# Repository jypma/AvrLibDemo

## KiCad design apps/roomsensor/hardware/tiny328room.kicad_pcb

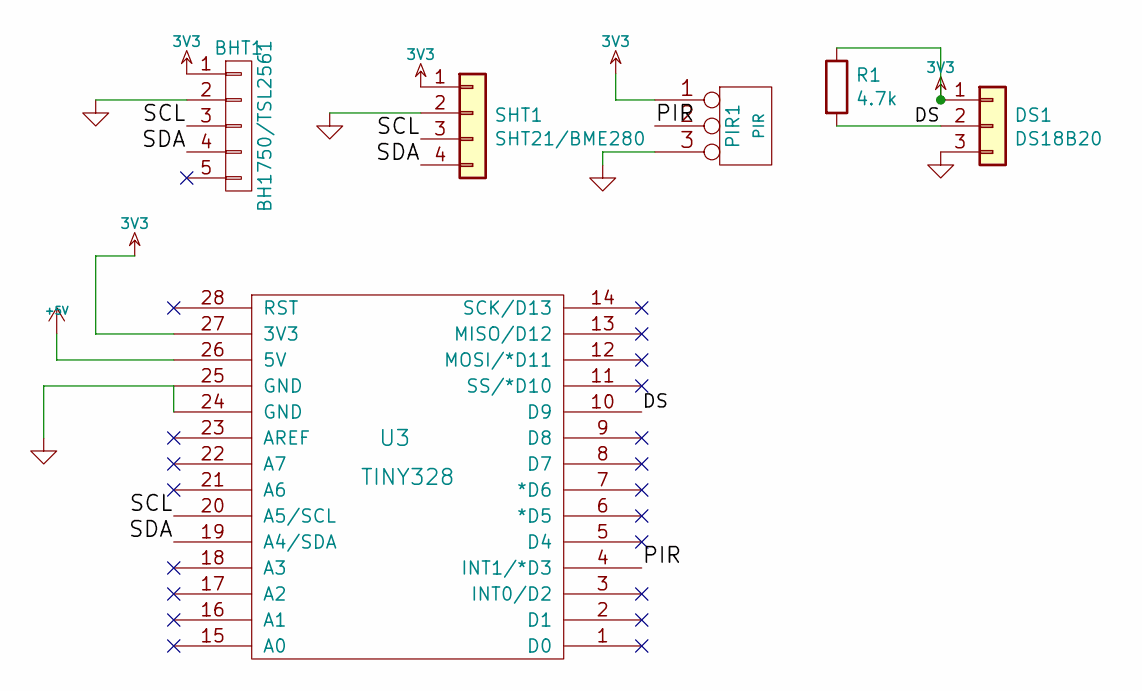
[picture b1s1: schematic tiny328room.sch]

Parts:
BHT1: BH1750/TSL2561; PinHeader_1x05_P2.54mm_Vertical
DS1: DS18B20; PinHeader_1x03_P2.54mm_Vertical
PIR1: PIR; PinHeader_1x03_P2.54mm_Vertical
R1: 4.7k; R_0603_1608Metric_Pad1.05x0.95mm_HandSolder
SHT1: SHT21/BME280; PinHeader_1x04_P2.54mm_Vertical
U3: TINY328; TINY328_CONN

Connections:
3V3: BHT1.1, DS1.1, PIR1.1, R1.1, SHT1.1, U3.27 (3V3)
+5V: U3.26 (5V)
/DS: DS1.2, R1.2, U3.10 (D9)
/PIR: PIR1.2 (PM), U3.4 (INT1/*D3)
/SCL: BHT1.3, SHT1.3, U3.20 (A5/SCL)
/SDA: BHT1.4, SHT1.4, U3.19 (A4/SDA)
GND: BHT1.2, DS1.3, PIR1.3, SHT1.2, U3.24 (GND), U3.25 (GND)

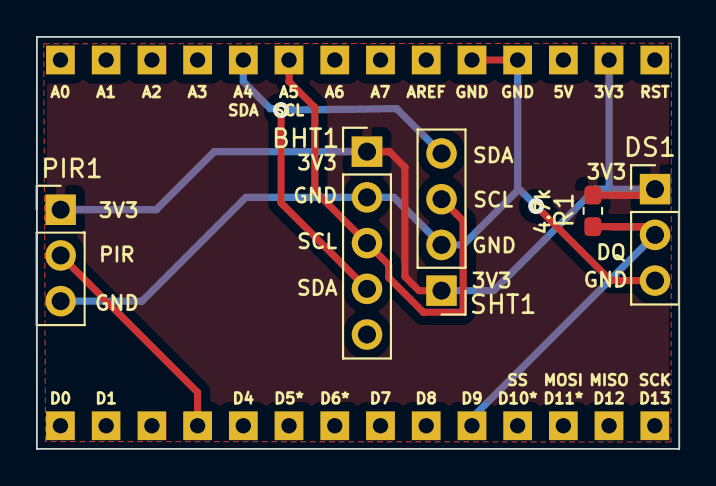
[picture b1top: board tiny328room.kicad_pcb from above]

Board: 2 copper layers, 35.7 x 22.9 mm, 6 parts (0 on the bottom side), 6 nets.

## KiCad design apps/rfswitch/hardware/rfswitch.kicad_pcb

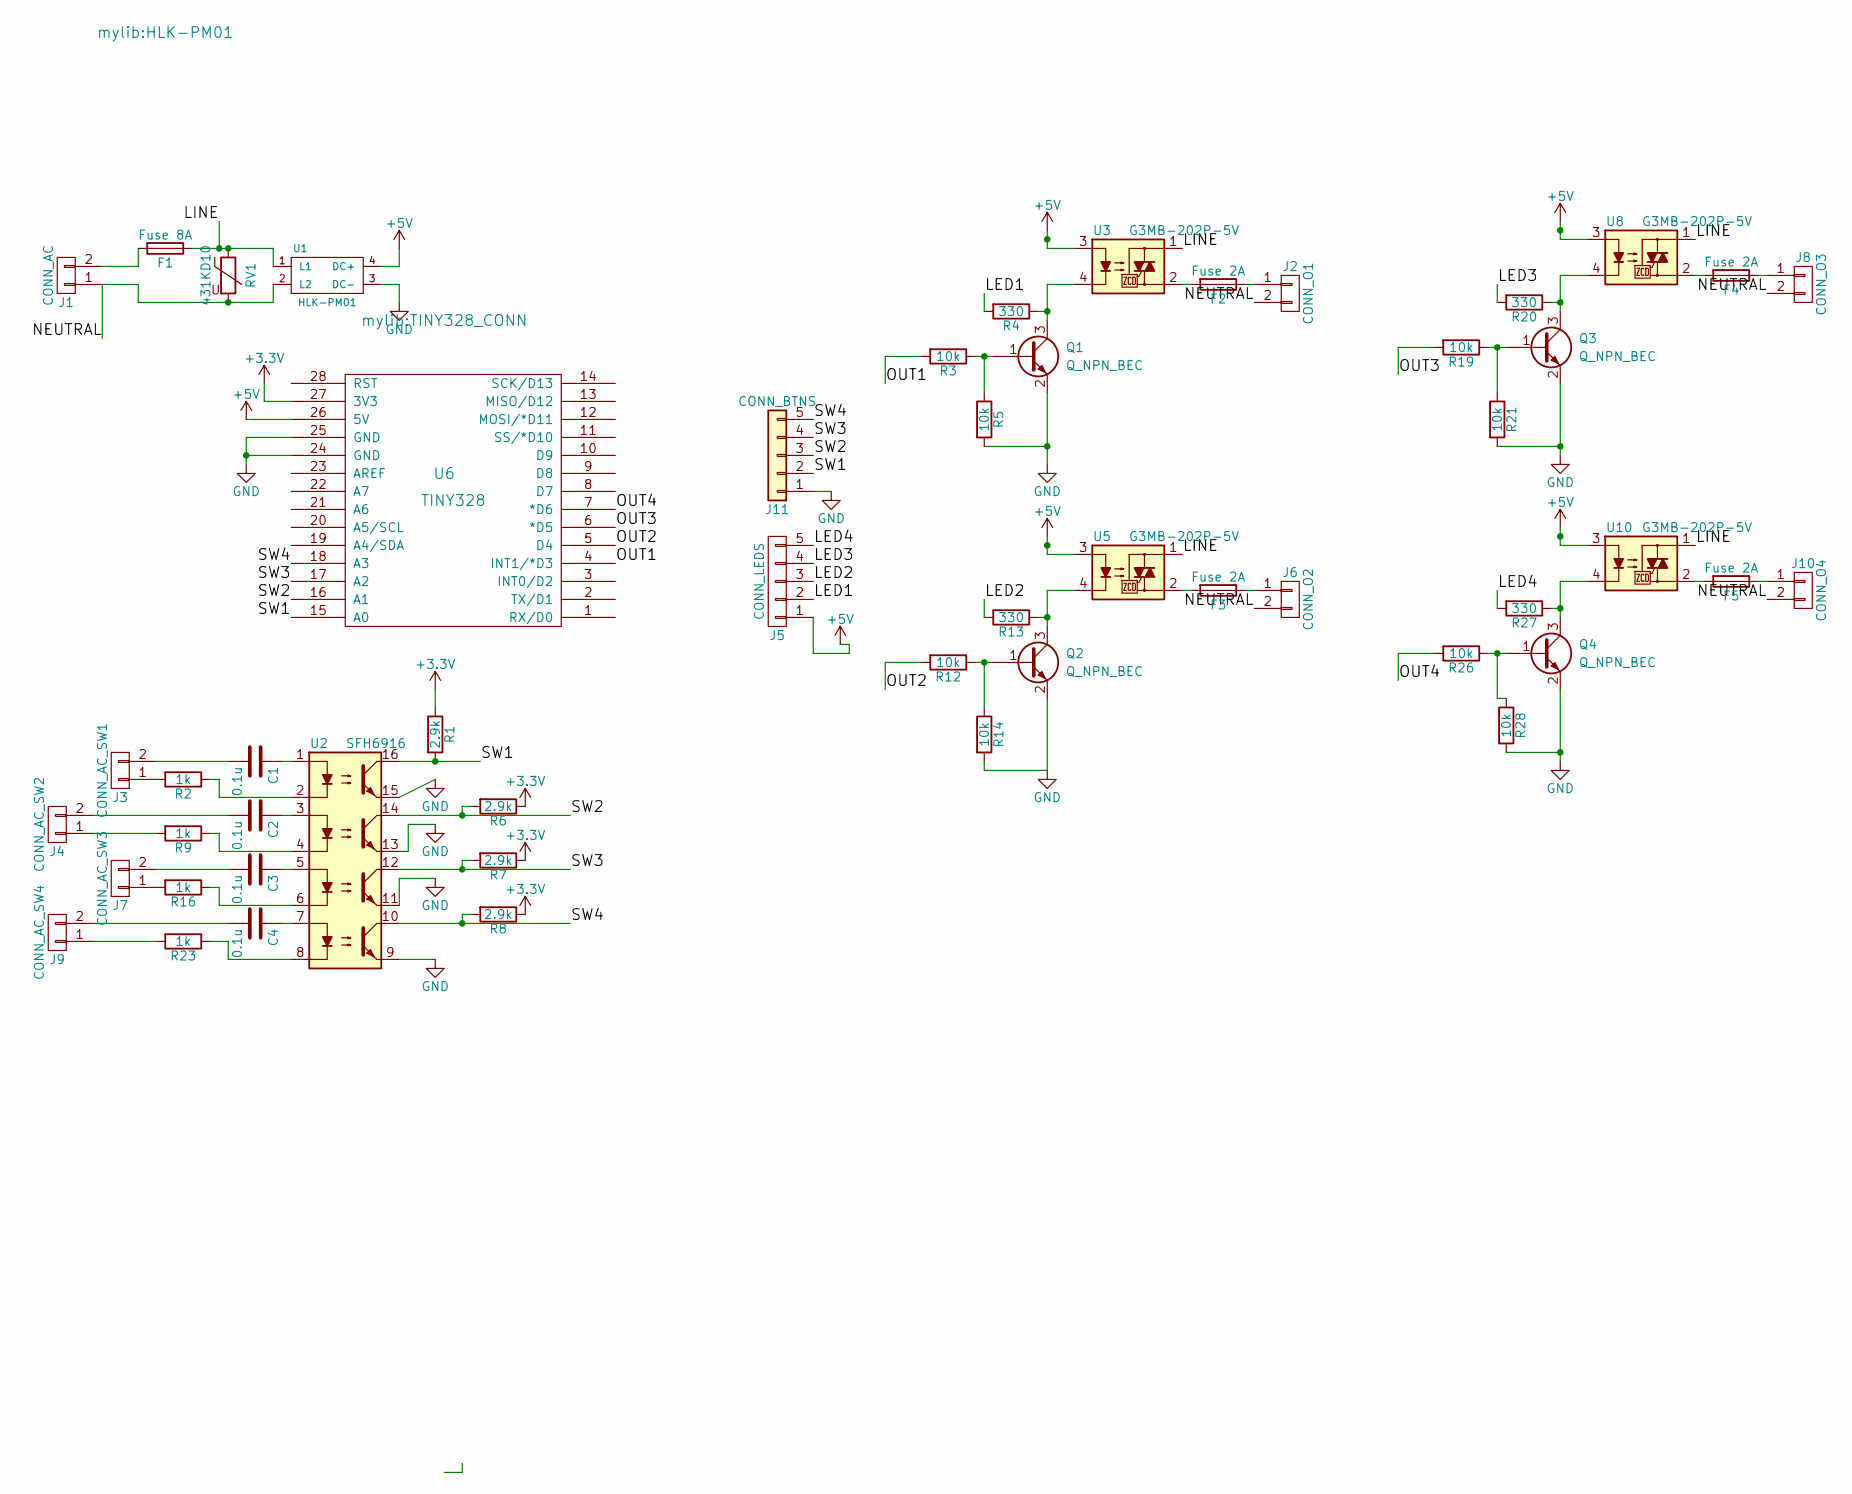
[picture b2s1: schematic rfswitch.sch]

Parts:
C1, C2, C3, C4: 0.1u; C_Rect_L16.5mm_W6mm_P15.00mm_MKT
F1: Fuse 8A; Fuseholder5x20_horiz_SemiClosed_Casing10x25mm
F2, F3, F4, F5: Fuse 2A; Fuseholder5x20_horiz_SemiClosed_Casing10x25mm
J1: CONN_AC; SCREW_CONN_5mm_1x2
J2: CONN_O1; SCREW_CONN_5mm_1x2
J3: CONN_AC_SW1; SCREW_CONN_5mm_1x2
J4: CONN_AC_SW2; SCREW_CONN_5mm_1x2
J5: CONN_LEDS; Pin_Header_Straight_1x05_Pitch2.54mm
J6: CONN_O2; SCREW_CONN_5mm_1x2
J7: CONN_AC_SW3; SCREW_CONN_5mm_1x2
J8: CONN_O3; SCREW_CONN_5mm_1x2
J9: CONN_AC_SW4; SCREW_CONN_5mm_1x2
J10: CONN_O4; SCREW_CONN_5mm_1x2
J11: CONN_BTNS; Pin_Header_Straight_1x05_Pitch2.54mm
Q1, Q2, Q3, Q4: Q_NPN_BEC; SOT-23
R1, R6, R7, R8: 2.9k; R_0603_HandSoldering
R2, R9, R16, R23: 1k; R_0603_HandSoldering
R3, R5, R12, R14, R19, R21, R26, R28: 10k; R_0603_HandSoldering
R4, R13, R20, R27: 330; R_0603_HandSoldering
RV1: 431KD10; RV_Disc_D7_W3.4_P5
U1: HLK-PM01
U2: SFH6916; SOP-16_4.4x10.4mm_Pitch1.27mm
U3, U5, U8, U10: G3MB-202P-5V; SIP4_Sharp-SSR_Pitch7.62mm_Straight
U6: TINY328; TINY328_CONN

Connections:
+3V3: R1.1, R6.1, R7.1, R8.1, U6.27 (3V3)
+5V: J5.1, U1.4 (DC+), U3.3, U5.3, U6.26 (5V), U8.3, U10.3; also elsewhere on the board
/LED1: J5.2, R4.2; also elsewhere on the board
/LED2: J5.3, R13.2; also elsewhere on the board
/LED3: J5.4, R20.2; also elsewhere on the board
/LED4: J5.5, R27.2; also elsewhere on the board
/LINE: F1.1, RV1.1, U1.1 (L1), U3.1, U5.1, U8.1, U10.1
/NEUTRAL: J1.1, J2.2, J6.2, J8.2, J10.2, RV1.2, U1.2 (L2)
/OUT1: R3.2, U6.4 (INT1/*D3)
/OUT2: R12.2, U6.5 (D4)
/OUT3: R19.2, U6.6 (*D5)
/OUT4: R26.2, U6.7 (*D6)
/SW1: J11.2, R1.2, U2.16, U6.15 (A0); also elsewhere on the board
/SW2: J11.3, R6.2, U2.14, U6.16 (A1); also elsewhere on the board
/SW3: J11.4, R7.2, U2.12, U6.17 (A2); also elsewhere on the board
/SW4: J11.5, R8.2, U2.10, U6.18 (A3); also elsewhere on the board
GND: J11.1, Q1.2 (E), Q2.2 (E), Q3.2 (E), Q4.2 (E), R5.2, R14.2, R21.2, R28.2, U1.3 (DC-), U2.9, U2.11, U2.13, U2.15, U6.24 (GND), U6.25 (GND); also elsewhere on the board
unnamed: C1.1, U2.1
unnamed: C1.2, J3.2
unnamed: C2.1, U2.3
unnamed: C2.2, J4.2
unnamed: C3.1, U2.5
unnamed: C3.2, J7.2
unnamed: C4.1, U2.7
unnamed: C4.2, J9.2
unnamed: F1.2, J1.2
unnamed: F2.1, J2.1
unnamed: F2.2, U3.2
unnamed: F3.1, J6.1
unnamed: F3.2, U5.2
unnamed: F4.1, J8.1
unnamed: F4.2, U8.2
unnamed: F5.1, J10.1
unnamed: F5.2, U10.2
unnamed: J3.1, R2.2
unnamed: J4.1, R9.2
unnamed: J7.1, R16.2
unnamed: J9.1, R23.2
unnamed: Q1.1 (B), R3.1, R5.1
unnamed: Q1.3 (C), R4.1, U3.4
unnamed: Q2.1 (B), R12.1, R14.1
unnamed: Q2.3 (C), R13.1, U5.4
unnamed: Q3.1 (B), R19.1, R21.1
unnamed: Q3.3 (C), R20.1, U8.4
unnamed: Q4.1 (B), R26.1, R28.1
unnamed: Q4.3 (C), R27.1, U10.4
unnamed: R2.1, U2.2
unnamed: R9.1, U2.4
unnamed: R16.1, U2.6
unnamed: R23.1, U2.8

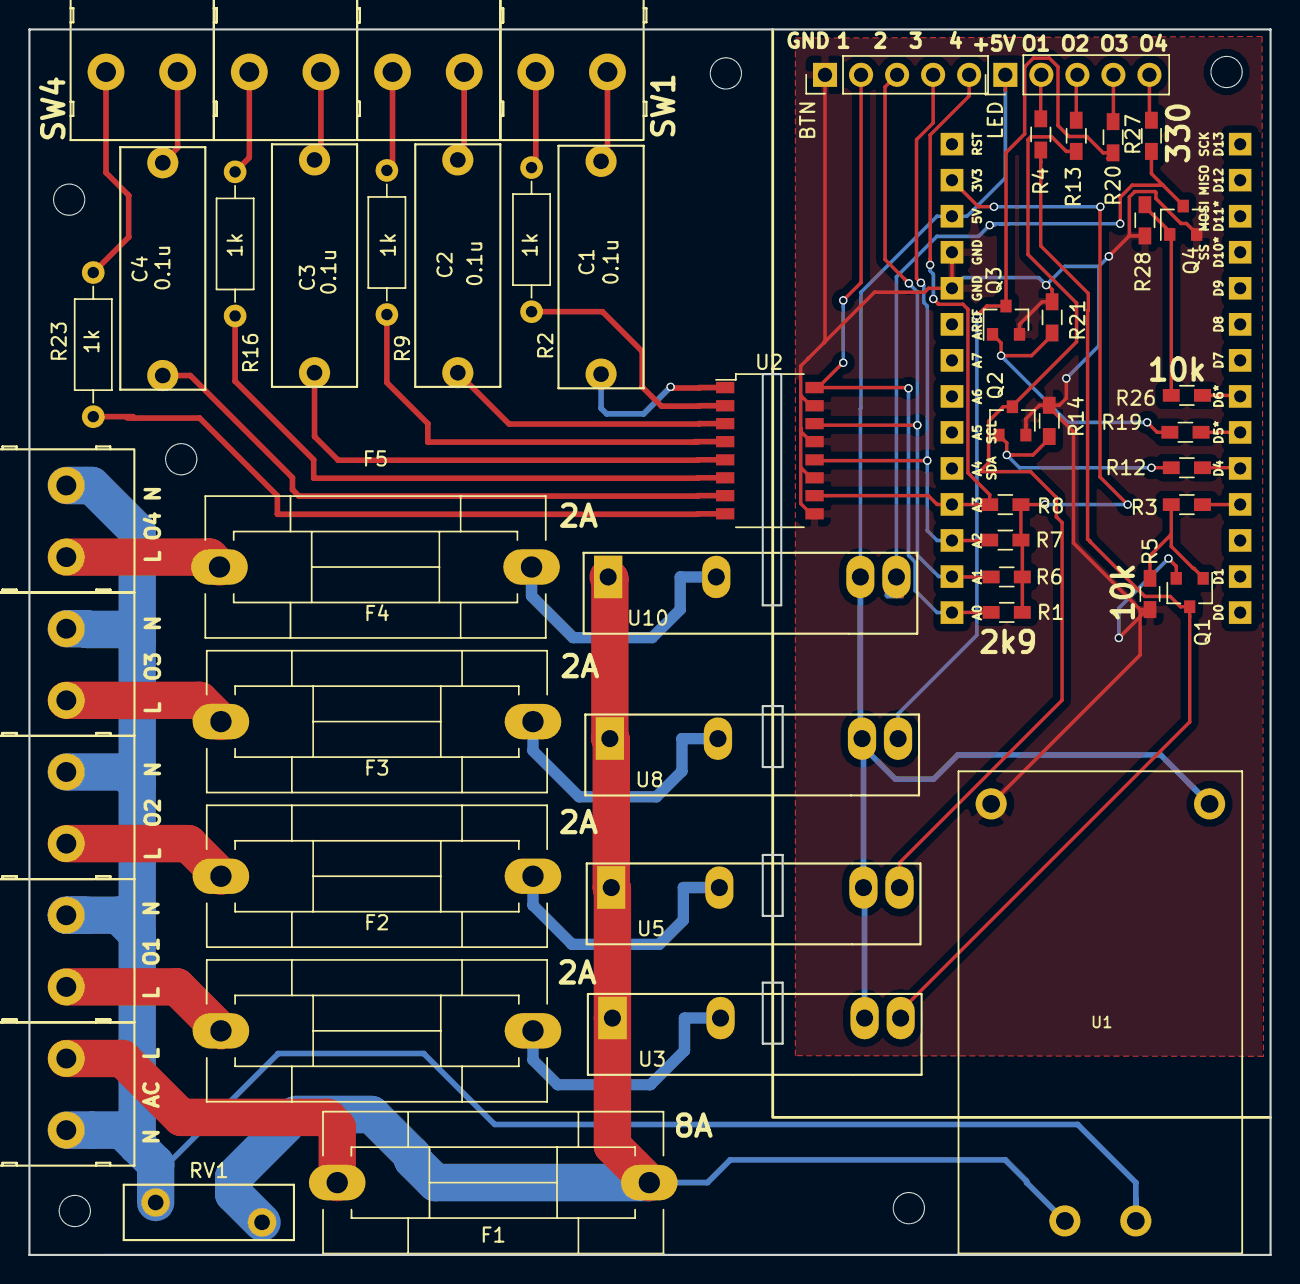
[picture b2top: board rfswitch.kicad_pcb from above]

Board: 2 copper layers, 87.5 x 86.4 mm, 52 parts (0 on the bottom side), 50 nets.

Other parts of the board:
BTN: CONN_BTNS; Pin_Header_Straight_1x05_Pitch2.54mm
LED: CONN_LEDS; Pin_Header_Straight_1x05_Pitch2.54mm

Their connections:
+5V: LED.1; also elsewhere on the board
/LED1: LED.2; also elsewhere on the board
/LED2: LED.3; also elsewhere on the board
/LED3: LED.4; also elsewhere on the board
/LED4: LED.5; also elsewhere on the board
/SW1: BTN.2; also elsewhere on the board
/SW2: BTN.3; also elsewhere on the board
/SW3: BTN.4; also elsewhere on the board
/SW4: BTN.5; also elsewhere on the board
GND: BTN.1; also elsewhere on the board

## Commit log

2015-01-11 initial commit of blink
2015-01-16 update for template changes
2015-03-31 add infrared decoder example
2015-04-10 fix up IRDecode build settings
2015-04-27 fix undefined use of overflowing atoi. Add configurable repeatability.
2015-04-27 updates for time units DSL. add ultrasound module demo.
2015-09-02 Updates for refactored AvrLib First release of ESP8266 proxy radio center OOK decoder serial tester
2016-01-13 Fix ESP8266 as proxy (code now maintained at Tiny328-proxy) Add lamp and flashlight demos
2016-05-09 Misc updates
2016-06-27 move to push more code into AvrLib
2017-03-12 mass commit for AvrLib major update
2017-04-04 Add a working makefile for doorsensor
2017-04-04 re-build avrlib when linking
2017-04-04 add temperature support
2017-04-04 ignore eeprom files by default since they can be sensitive
2017-04-04 remove eclipse files from source control, makefiles only now
2017-04-04 add serial target to do debugging
2017-04-07 commonize makefiles
2017-04-07 reset door sensors to retransmit 1 minute
2017-04-15 Commonize make files
2017-05-08 add rfswitch, move tools around
2017-05-08 sender ids are now maintained here
2017-05-13 add nimh charger for solar cell
2017-05-13 don't listen to PIR sensor as supply voltage gets real low
2017-05-15 Add radio support to send out charge level, and receive on/off of channels
2017-05-15 Moved old stuff out of the way
2017-05-15 add old apps/inc moved over from AvrLib
2017-05-19 updat eeeprom
2017-05-19 Set initial temperature before sending out first packet
2017-05-31 Enable radio, and be more reliable when transmitting
2017-05-31 Make baud rate configurable
2017-06-01 Deprecate auto_var and start to use explicit types
    auto_var causes an internal compiler error on avr-gcc 6+. So let's start
    to use more verbose explicit types for fields.
2017-06-02 emergency shutdown on low battery
2017-06-02 initialize logger first, and improve debug logging
2017-06-02 show AVR sizes ; save serial output to file by default
2017-06-10 Increase RF12 fifo buffers to allow both send and receive Turn off outputs on low and critical battery Ignore unused RF12 packets
2017-06-10 Make LEDs more useful by displaying conn / send / recv status
2017-06-10 Add RF12 packet monitor with a single LED
2017-07-07 Add initial schematic and layout
2017-07-09 Announce with protobuf, UDP broadcast support
2017-07-09 Up layout to 3 channels
2017-08-04 Adjust footprints of AC connectors to measured sizes
2017-08-04 ignore backups
2017-08-04 Main fuse should be in line with everything. Started routing.
2017-08-13 Switch to quad optocoupler, almost lay-out board finished.
2017-09-04 Fix pulldown resistor on transistors that wasn't in the right position
2017-09-04 Add input possibilities
2017-09-04 Update flash baud rate to latest arduino bootloader default
2017-09-10 tweaks, proper use op Optional.
2017-09-10 Make programmer baud rate tweakable
2017-09-23 make sure updates arrive.
2017-09-23 Small update for AvrLib refactors
2017-09-29 Various fixes after first order
2018-01-26 Only listen in fixed time slots to save radio power
2018-01-26 Final board tweaks for construction, and first release of software
2018-01-26 Turns out optiboot doesn't do EEPROM anymore. For now, use IVRASP.
2018-04-26 Initial commit for garden watering system
2018-04-26 View disassembly, rtags shortcut, prepare to burn bootloader
2018-04-26 Program bootloader from makefile
2018-04-27 More fixes for Task refactoring (types branch of AvrLib)
2018-04-27 safe fuses before burning bootloader
2018-04-27 Add debug info to verify re-watering starts properly
2018-08-29 More channels in use now
2018-11-29 Slowly burn initial bootloader fuses
    Because factory ATMegas as SLOW!
2018-12-01 Use the normal first USB port
2018-12-20 Automatically select USB port
2018-12-20 Add heater sender ID reservation
2018-12-20 Add heater firmware
2019-04-26 WIP heater improvements and dimmer
2019-09-27 Gcc 9.1 workarounds for ICE
2019-12-05 Add ordered PCB to roomsensor
2020-12-18 General cleanup for revised case
2020-12-18 Upgrade serial port auto-selection
